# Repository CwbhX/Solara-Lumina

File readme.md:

# Solara Lumina

## Overview
Me trying to create a bright light to simulate the sun in my sun deprived apartment

## Features
- Really really bright

## Getting Started
Oh man are you sure

### Prerequisites

## Hardware Setup
TBD

## Usage and Testing
TBD

## Contributing
shoot me a dm

## Versioning

## Authors and Acknowledgments
- **Clement Hathaway** - *Initial design*

## Contact
shoot me another dm

## Project Status
Figuring it out

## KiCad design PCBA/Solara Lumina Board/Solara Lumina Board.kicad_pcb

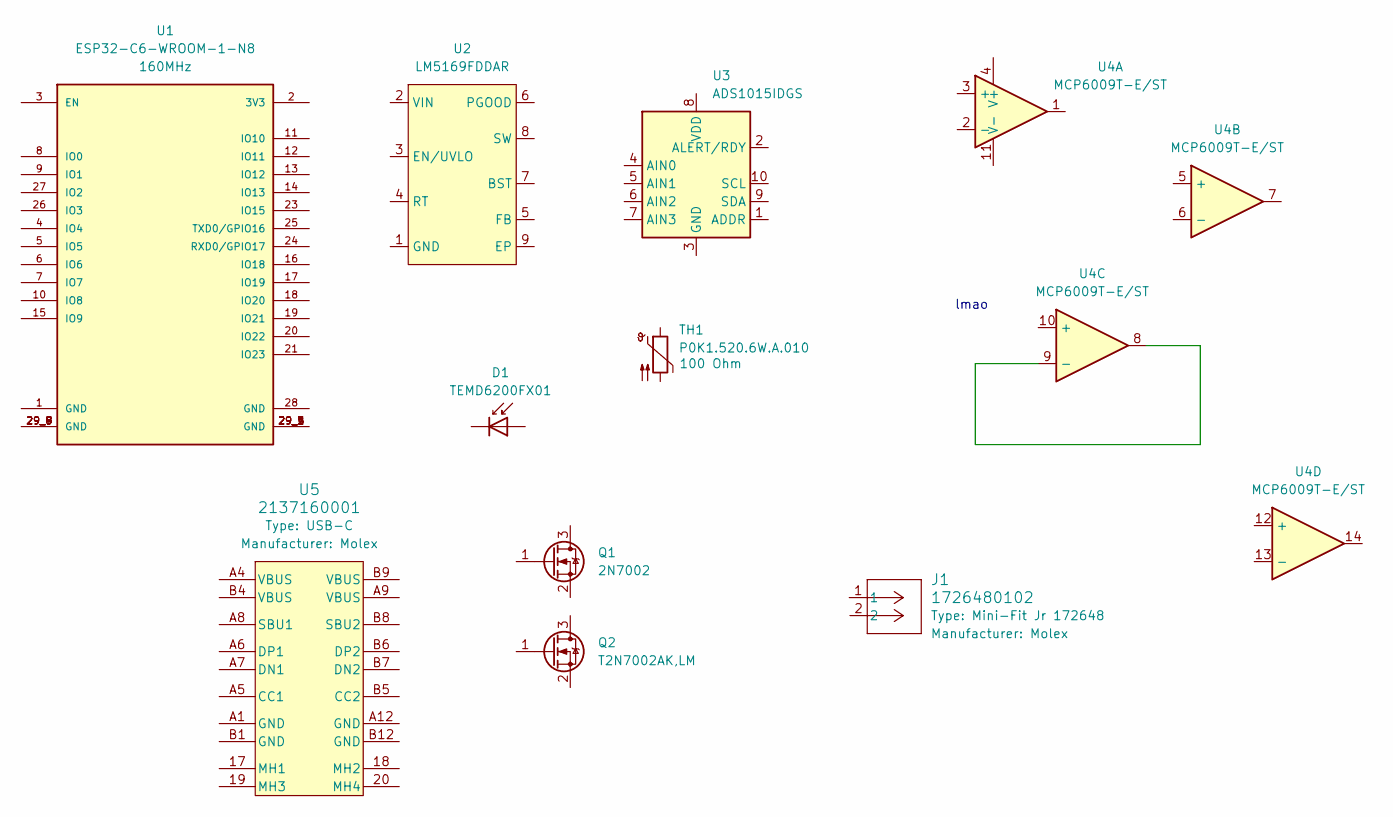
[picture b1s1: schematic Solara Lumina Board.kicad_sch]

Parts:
D1: TEMD6200FX01; PhotoDiode-0805; Reverse Voltage 16V; Current Rating 0.09uA; MPN TEMD6200FX01
J1: 1726480102; Molex_1726480102; Current Rating 12.5A; Voltage Rating 600V; MPN 1726480102
Q1: 2N7002; SOT-23
Q2: T2N7002AK,LM; SOT-23; Current Rating 200mA; Power Rating 320mW; MPN T2N7002AK,LM
TH1: P0K1.520.6W.A.010; PinHeader_1x02_P2.00mm_Vertical; MPN P0K1.520.6W.A.010
U1: ESP32-C6-WROOM-1-N8; PARTREV 1.0
U2: LM5169FDDAR; TI_SO-PowerPAD-8; MPN LM5169FDDAR
U3: ADS1015IDGS; TSSOP-10_3x3mm_P0.5mm
U4: MCP6009T-E/ST; TSSOP-14_4.4x5mm_P0.65mm; MPN MCP6009T-E/ST
U5: 2137160001; USB-C-2137160001; Current Rating 5A; Voltage Rating 30V; MPN 2137160001

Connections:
unnamed: U1.29_1 (GND), U1.29_2 (GND), U1.29_3 (GND), U1.29_4 (GND), U1.29_5 (GND)
unnamed: U1.29_6 (GND), U1.29_7 (GND), U1.29_8 (GND), U1.29_9 (GND)
unnamed: U4.8, U4.9 (-)

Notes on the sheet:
lmao

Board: 6 copper layers, 11 parts (0 on the bottom side), 3 nets, no tracks yet.

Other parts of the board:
TH1#2: P0K1.520.6W.A.010; PinHeader_1x02_P2.00mm_Vertical

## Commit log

2024-01-15 research stuff
2024-05-17 Added KiCAD Project
2024-05-18 Updated outline
2024-06-02 imported outline
2024-06-18 Added ESP32-C6 and increased board size
2024-06-19 Part Research
2024-06-20 Adding parts!
2024-06-21 Added the op-amp eek
2024-06-22 Added more parts and adjusted board outline
